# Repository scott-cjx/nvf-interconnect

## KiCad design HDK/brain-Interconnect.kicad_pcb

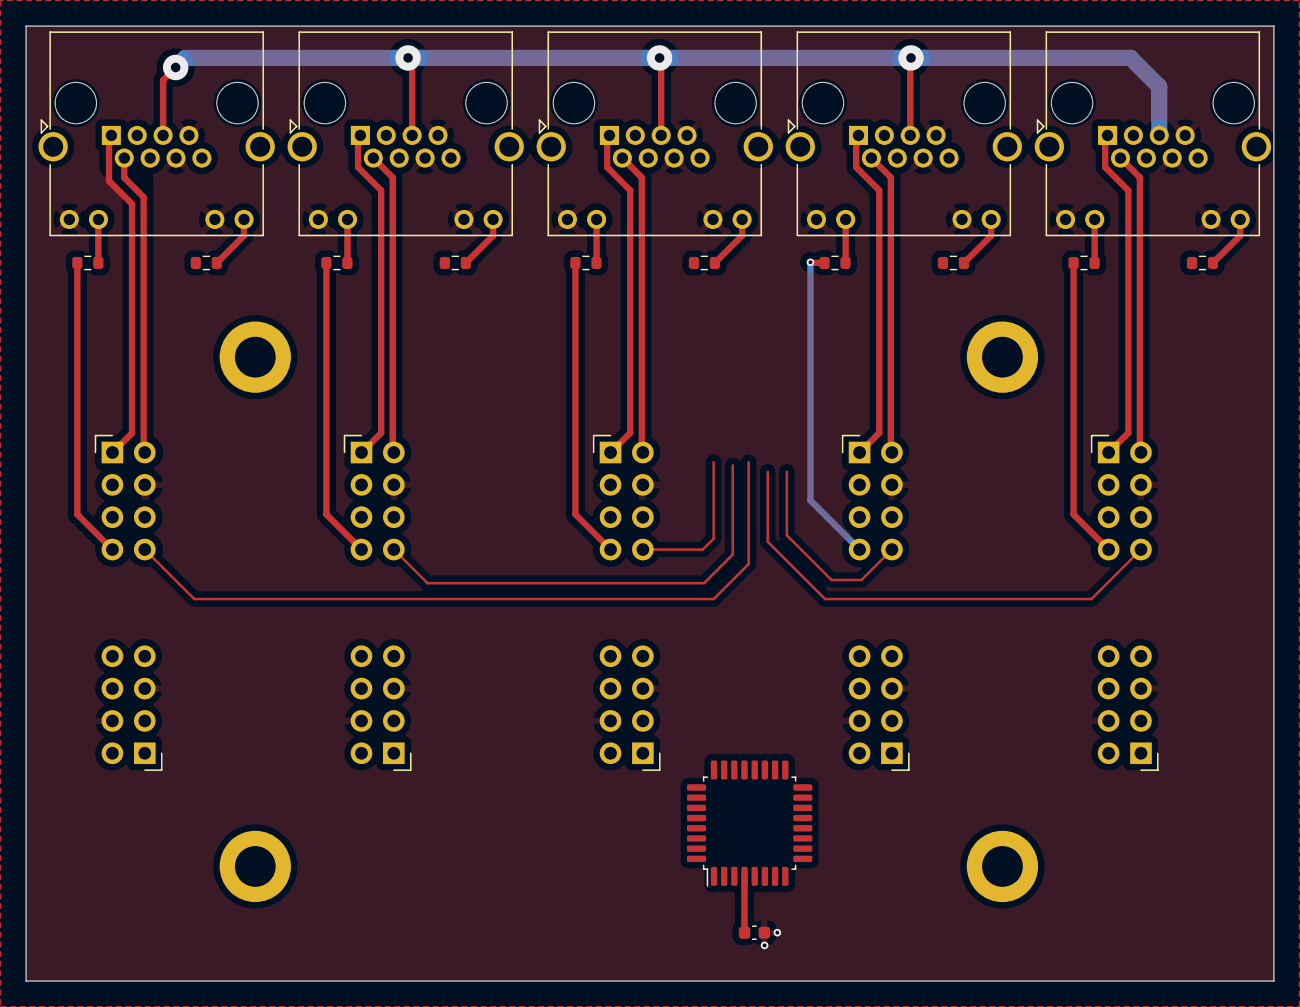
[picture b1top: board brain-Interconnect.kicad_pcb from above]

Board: 2 copper layers, 98.0 x 75.0 mm, 27 parts (0 on the bottom side), 26 nets.

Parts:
C101: C; C_0603_1608Metric
J201, J202, J301, J302, J401, J402, J501, J502, J601, J602: Conn_02x04_Odd_Even; 2x04V-H
J203, J303, J403, J503, J603: 8P8C_LED; RJ45_Amphenol_RJHSE538X
R201, R202, R301, R302, R401, R402, R501, R502, R601, R602: 330; R_0603_1608Metric
U101: STM32G030K6Tx; LQFP-32_7x7mm_P0.8mm

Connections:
+3V3: C101.1, U101.4 (VDD)
/V1: J201.3, J203.5, J301.3, J303.5, J401.3, J403.5, J501.3, J503.5, J601.3, J603.5
/V2: J201.6, J203.4, J301.6, J303.4, J401.6, J403.4, J501.6, J503.4, J601.6, J603.4
/interconnect-brain1/CAN2_H: J202.1, J203.1
/interconnect-brain1/CAN2_L: J202.2, J203.2
/interconnect-brain1/CAN_H: J201.1, J201.8, J301.1, J301.8, J401.1, J401.8, J501.1, J501.8, J601.1, J601.8
/interconnect-brain1/CAN_L: J201.2, J201.7, J301.2, J301.7, J401.2, J401.7, J501.2, J501.7, J601.2, J601.7
/interconnect-brain2/CAN2_H: J302.1, J303.1
/interconnect-brain2/CAN2_L: J302.2, J303.2
/interconnect-brain3/CAN2_H: J402.1, J403.1
/interconnect-brain3/CAN2_L: J402.2, J403.2
/interconnect-brain4/CAN2_H: J502.1, J503.1
/interconnect-brain4/CAN2_L: J502.2, J503.2
/interconnect-brain5/CAN2_H: J602.1, J603.1
/interconnect-brain5/CAN2_L: J602.2, J603.2
GND: C101.2, J201.4, J201.5, J202.4, J202.5, J203.6, J203.7, J203.9, J203.11, J301.4, J301.5, J302.4, J302.5, J303.6, J303.7, J303.9, J303.11, J401.4, J401.5, J402.4, J402.5, J403.6, J403.7, J403.9, J403.11, J501.4, J501.5, J502.4, J502.5, J503.6, J503.7, J503.9, J503.11, J601.4, J601.5, J602.4, J602.5, J603.6, J603.7, J603.9, J603.11
unnamed: J203.10, R201.1
unnamed: J203.12, R202.1
unnamed: J303.10, R301.1
unnamed: J303.12, R302.1
unnamed: J403.10, R401.1
unnamed: J403.12, R402.1
unnamed: J503.10, R501.1
unnamed: J503.12, R502.1
unnamed: J603.10, R601.1
unnamed: J603.12, R602.1

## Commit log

2023-12-20 Initialize gh-pages
2023-12-20 Moving files docs/* LICENSE using main
2023-12-20 Deploying to gh-pages from @ scott-cjx/nvf-interconnect@adb4f32846036676b7f5b41d926da0bad03cd06b 🚀
2023-12-20 added interconnect
2023-12-20 Deploying to gh-pages from @ scott-cjx/nvf-interconnect@15d64d0e0a1cb280dd28261e19c6c428e6772c63 🚀
